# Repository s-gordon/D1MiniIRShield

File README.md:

# D1 Mini IR Shield

## Description

A simple board for controlling IR devices using an ESP8266 DevKit and ESPHome.

I wanted a way to control my IR devices, such as TVs and air conditioners, without the need for cloud enabled devices or inflexible solutions such as Broadlink Universal Remotes. Moreover, I wanted something that could run ESPHome so that I can customize it as I see fit, and access the multitude of free and public libraries that are available. The solution was to develop my own board: the D1 Mini IR Shield!

## Getting Started with ESPhome

Open ESPhome and create a new device config as follows. You will need to define the following secrets in ESPhome:

- wifi_ssid
- wifi_password
- apikey
- ota_password
- gateway
- subnet

```yaml
substitutions:
  name: "irremote-office"
  room: "Office"
  friendly_name: "IRRemote ${room}"
  project_name: "D1MiniIRRemote.Remote"
  project_version: v1.0rc1

packages:
  remote_package:
    url: https://github.com/s-gordon/D1MiniIRShield
    ref: v1.0rc1
    refresh: 1d
    files:
      - esphome/packages/base.yaml
      # choose one of these as appropriate
      # comment out the others
      - esphome/packages/daikin.yaml
      - esphome/packages/coolix.yaml
      - esphome/packages/fujitsu.yaml

# Enable Home Assistant API
api:
  encryption:
    key: !secret apikey

ota:
  password: !secret ota_password

wifi:
  ssid: !secret wifi_ssid
  password: !secret wifi_password
  fast_connect: on
  manual_ip:
    static_ip: !secret irremote_office_ip
    gateway: !secret gateway
    subnet: !secret subnet
```

## Preview

| 3D | 2D |
| -- | -- |
|  |  |

## Credits

Created and maintained by Shane Gordon (@s-gordon).

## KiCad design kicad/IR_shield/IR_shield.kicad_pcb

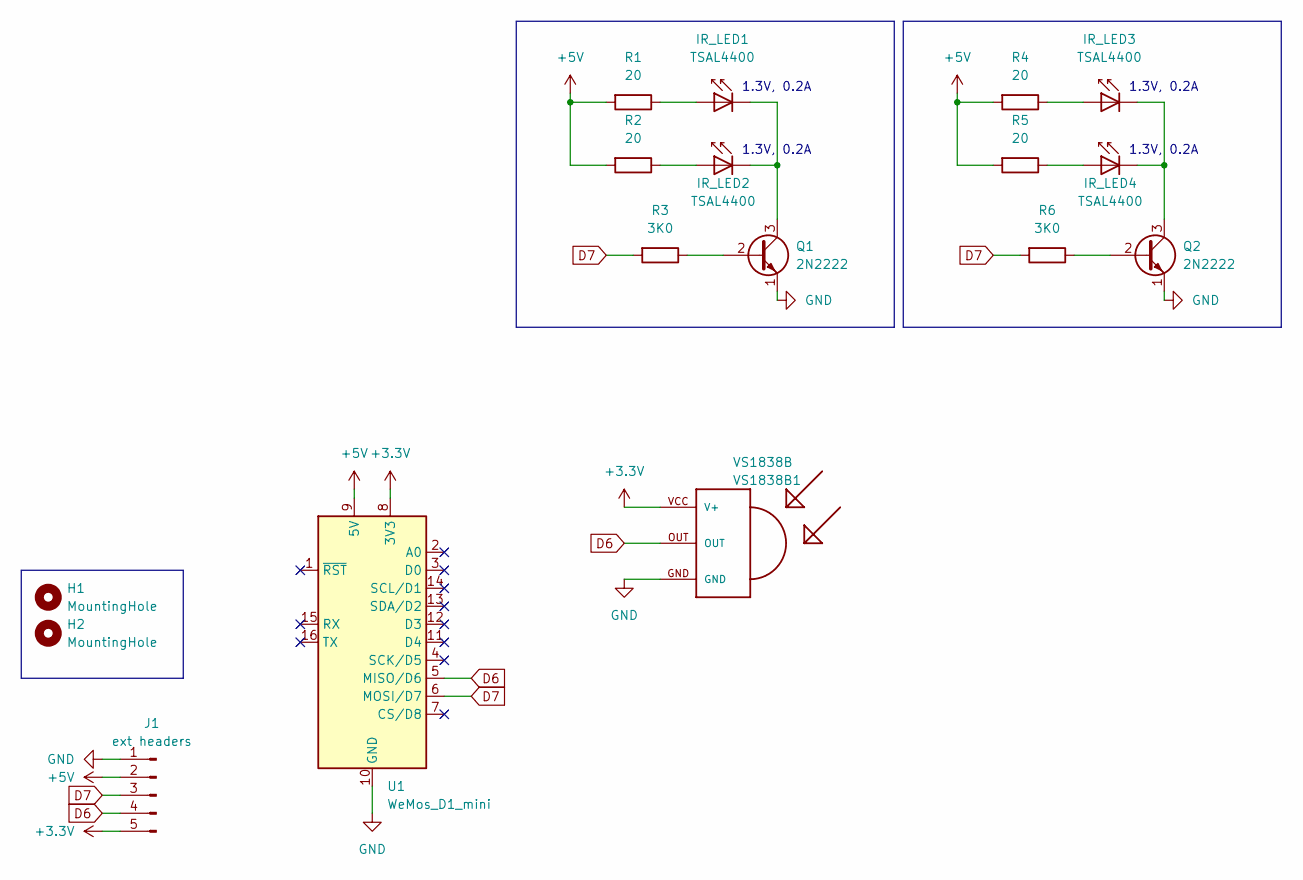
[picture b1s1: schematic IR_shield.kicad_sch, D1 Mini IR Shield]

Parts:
H1, H2: MountingHole; MountingHole_3.2mm_M3
IR_LED1, IR_LED2, IR_LED3, IR_LED4: TSAL4400; LED_D3.0mm
J1: ext headers; PinHeader_1x05_P2.54mm_Vertical
Q1, Q2: 2N2222; TO-92_Inline
R1, R2, R4, R5: 20; R_0805_2012Metric
R3, R6: 3K0; R_0805_2012Metric
U1: WeMos_D1_mini; WEMOS_D1_mini_light
VS1838B1: VS1838B; TSOP18XX

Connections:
+3V3: J1.5, U1.8 (3V3), VS1838B1.VCC (V+)
+5V: J1.2, R1.2, R2.2, R4.2, R5.2, U1.9 (5V)
D6: J1.4, U1.5 (MISO/D6), VS1838B1.OUT
D7: J1.3, R3.2, R6.2, U1.6 (MOSI/D7)
GND: J1.1, Q1.1 (E), Q2.1 (E), U1.10 (GND), VS1838B1.GND
unnamed: IR_LED1.2 (A), R1.1
unnamed: IR_LED1.1 (K), IR_LED2.1 (K), Q1.3 (C)
unnamed: IR_LED2.2 (A), R2.1
unnamed: IR_LED3.2 (A), R4.1
unnamed: IR_LED3.1 (K), IR_LED4.1 (K), Q2.3 (C)
unnamed: IR_LED4.2 (A), R5.1
unnamed: Q1.2 (B), R3.1
unnamed: Q2.2 (B), R6.1

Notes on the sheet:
1.3V, 0.2A

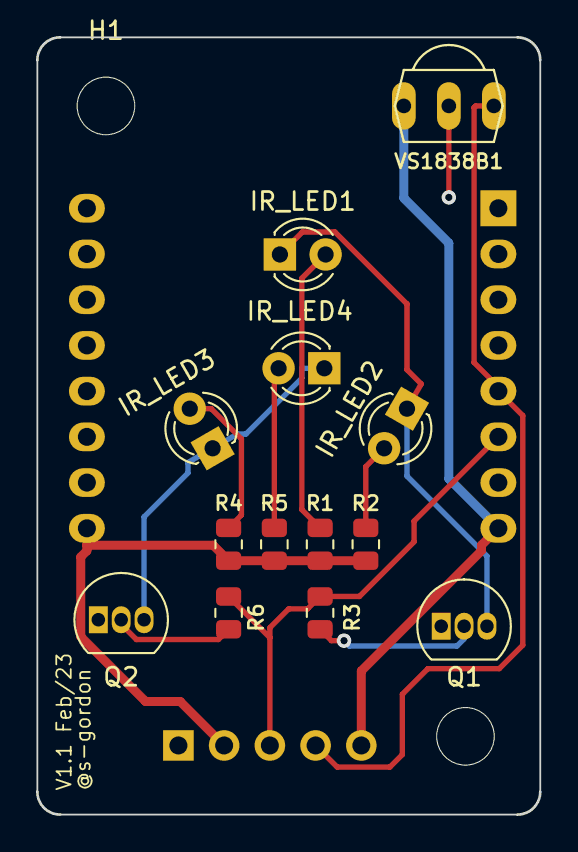
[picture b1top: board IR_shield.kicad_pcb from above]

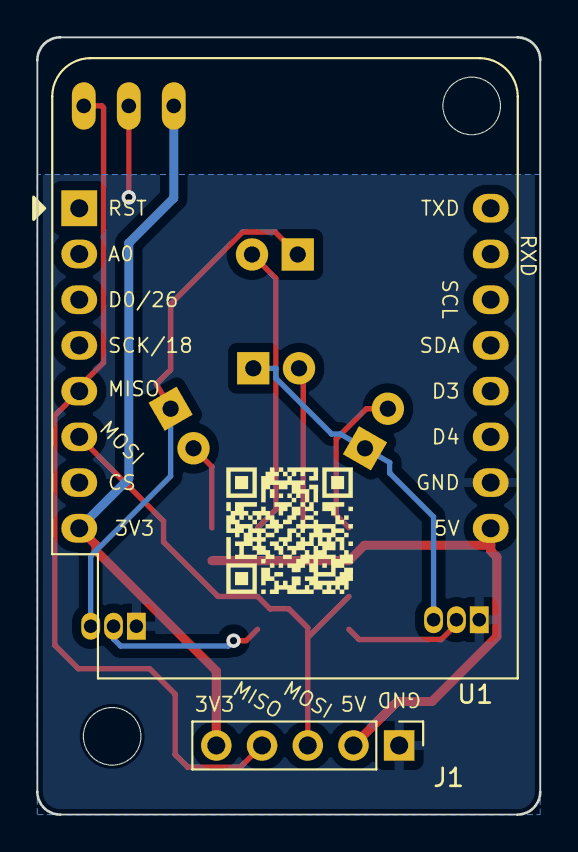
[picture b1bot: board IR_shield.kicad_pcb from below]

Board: 2 copper layers, 27.9 x 43.2 mm, 17 parts (2 on the bottom side), 13 nets.

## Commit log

2023-01-27 Added kicad files.
2023-01-27 Added QR code linking to GitHub repo to print on PCB.
2023-01-27 Added case STL.
2023-01-27 Reworked routing and added male header pins.
2023-01-27 Added logo to lid. Added nail hold for removing lid.
2023-01-27 Added ignore rules.
2023-01-27 Corrected footprint for female headers from male headers.
2023-01-27 Added schematics and 3D model for PCB.
2023-01-29 Expanded margins of PCB to avoid clash with D1 Mini. 5 pin male headers changed to flat rather than sticking up.
2023-01-29 Fixed bad PCB image. Whoops.
2023-02-18 Reworked design to add 4 IR LEDs.
2023-02-21 Moved the QR code to a better location on the PCB. Likewise with text information.
2023-02-21 Updated PCB pictures to 1.0-rc2.
2023-02-21 Updated PCB pictures to 1.0-rc1.
2023-02-21 Added ESPHome config #1
2023-02-21 Added dashboard import
2023-02-21 Added brief description.
2023-02-21 Added credits to README
2023-04-01 Reworked design
2023-04-27 Added ESPHome config
2023-04-27 Separated out AC unit
2023-04-27 Removed receiver ID on coolix
2023-04-27 Dropped AP pass
2023-10-21 Added a minimal ESPhome example to README
2024-02-09 Added Fujitsu AC
